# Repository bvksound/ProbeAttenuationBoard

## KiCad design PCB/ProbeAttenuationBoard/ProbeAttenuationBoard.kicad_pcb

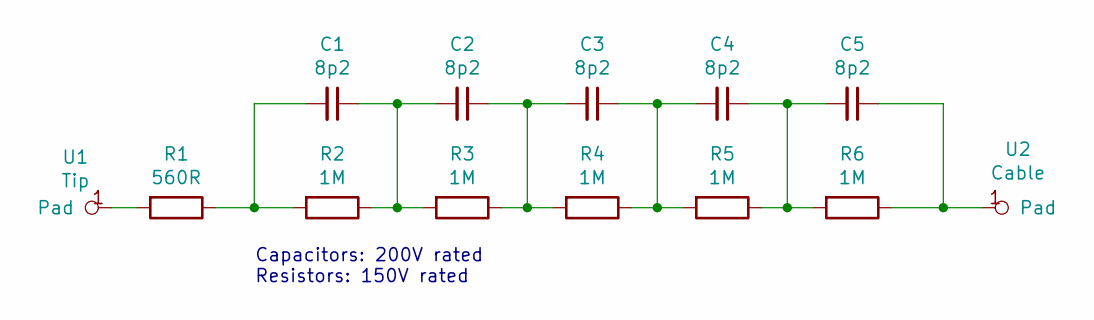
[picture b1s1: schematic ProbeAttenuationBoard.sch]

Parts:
C1, C2, C3, C4, C5: 8p2; C_0805_2012Metric
R1: 560R; R_0805_2012Metric
R2, R3, R4, R5, R6: 1M; R_0805_2012Metric
U1: Tip; PAD_1_8x4mm_Single
U2: Cable; PAD_1_8x4mm_Single

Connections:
unnamed: C1.1, C2.2, R2.1, R3.2
unnamed: C1.2, R1.1, R2.2
unnamed: C2.1, C3.2, R3.1, R4.2
unnamed: C3.1, C4.2, R4.1, R5.2
unnamed: C4.1, C5.2, R5.1, R6.2
unnamed: C5.1, R6.1, U2.1
unnamed: R1.2, U1.1

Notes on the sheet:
Capacitors: 200V rated Resistors: 150V rated

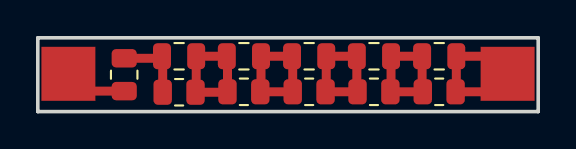
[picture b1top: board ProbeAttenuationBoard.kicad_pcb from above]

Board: 2 copper layers, 27.8 x 4.1 mm, 13 parts (0 on the bottom side), 7 nets.

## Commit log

2021-08-06 rev1 added
